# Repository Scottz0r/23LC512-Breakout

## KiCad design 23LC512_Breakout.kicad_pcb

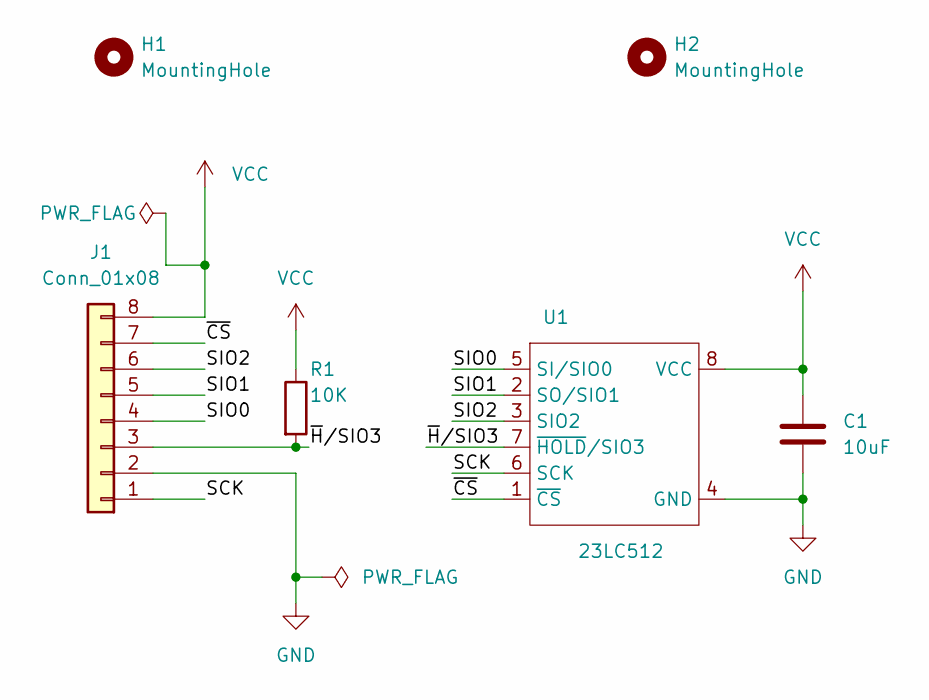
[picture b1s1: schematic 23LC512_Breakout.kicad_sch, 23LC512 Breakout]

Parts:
C1: 10uF; C_1206_3216Metric
H1, H2: MountingHole; MountingHole_2.5mm
J1: Conn_01x08; PinHeader_1x08_P2.54mm_Vertical
R1: 10K; R_1206_3216Metric
U1: 23LC512; SO-8_3.9x4.9mm_P1.27mm

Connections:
/SCK: J1.1, U1.6 (SCK)
/SIO0: J1.4, U1.5 (SI/SIO0)
/SIO1: J1.5, U1.2 (SO/SIO1)
/SIO2: J1.6, U1.3 (SIO2)
/~CS: J1.7, U1.1 (~CS)
/~H/SIO3: J1.3, R1.2, U1.7 (~HOLD/SIO3)
GND: C1.2, J1.2, U1.4 (GND)
VCC: C1.1, J1.8, R1.1, U1.8 (VCC)

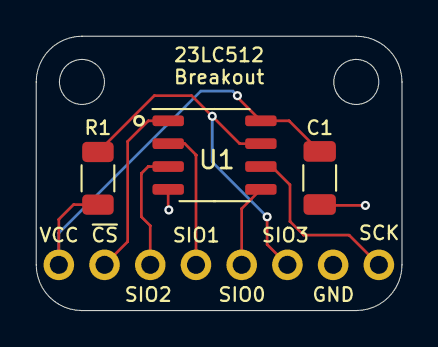
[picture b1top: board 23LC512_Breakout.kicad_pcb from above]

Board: 2 copper layers, 20.3 x 15.2 mm, 6 parts (0 on the bottom side), 8 nets.

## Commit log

2022-07-03 Adding files
    Adding project files
